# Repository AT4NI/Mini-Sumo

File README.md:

# Mini-Sumo
Codes and documentation for my minisumo robot.
It is focused on the development of competition robots made by me.
The repository will include: 3D models, code, PCB and electronic schematics.

**NOTE: The projects developed may have errors that will be corrected in the future.**

*The projects marked in italic are projects that are still on progress*

# Why did I make a repository?
It was made for fans of robotics competition, helping them to get access to information.
I would like any fan to be able to make their own robots and have fun.
Also, I would like to have version control of my projects.

# Folders

## Robots
- I7ACH1: Minisumo with 4 sensors and 2 line sensor
- GYU: Minisumo with 4 sensors and 2 line sensor
- SIRUKI: Microsumo with 3 sensors and 1 line sensor
- ALO: Microsumo with 2 sensors and 1 line sensor
- ATANI: Amateur RC Minisumo
## PCB's
- Main boards:
  - *SIRUKI: PCB designed for micro-sumo.*

## Code
- I7ach1: main code used for minisumo robot I7ach1 which uses a ESP32-C3 as the main board
- GYU: main code used for minisumo robot GYU which uses a ARDUINO NANO as the main controller
- *SIRUKI: main code used for microsumo robot SIRUKI which uses a ESP32-C3 as the main controller*
- ALO: main code used for microsumo robot ALO which uses a ESP32-C3 as the main controller
- ATANI: main code used for minisumo robot ATANI which uses a ARDUINO NANO as the main controller
## 3D Data
- Robots
	- I7ach1: Base of the robot is steel and the case is PLA.
	- *SIRUKI: Base of the robot is brass and the case is made of PLA*
	- *ALO: The robot is made of PLA*
	- ATANI: The robot is made of PLA.

# Software that I use
The software I use, most of them are free license and easy to use.
The formats of the files are the most friendly with the other types of software used.

- 3D data: I mainly use SOLIDWORKS and FUSION 360 but I upload the files in .IGES and .STL so you can use any 3D CAD software and slicer software out there to modify and/or print the parts.
- PCB's: I upload the gerbers in zip format for easy fabrication **[KiCad](https://www.kicad.org/)** which is a free and open source EDA.
- Code: I use ARDUINO IDE **[ARDUINO IDE ](https://www.arduino.cc/en/Guide)**  

---

*Developing robots, continue...*

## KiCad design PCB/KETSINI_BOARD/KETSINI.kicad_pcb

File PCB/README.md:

# PCB
### KETSINI_V1
PCB designed for micro-sumo.
 - **Brain:** ESP32 C3 Super Mini
 - **Driver:** DRV8871
 - **Voltage Regulator:** AMS1117-5

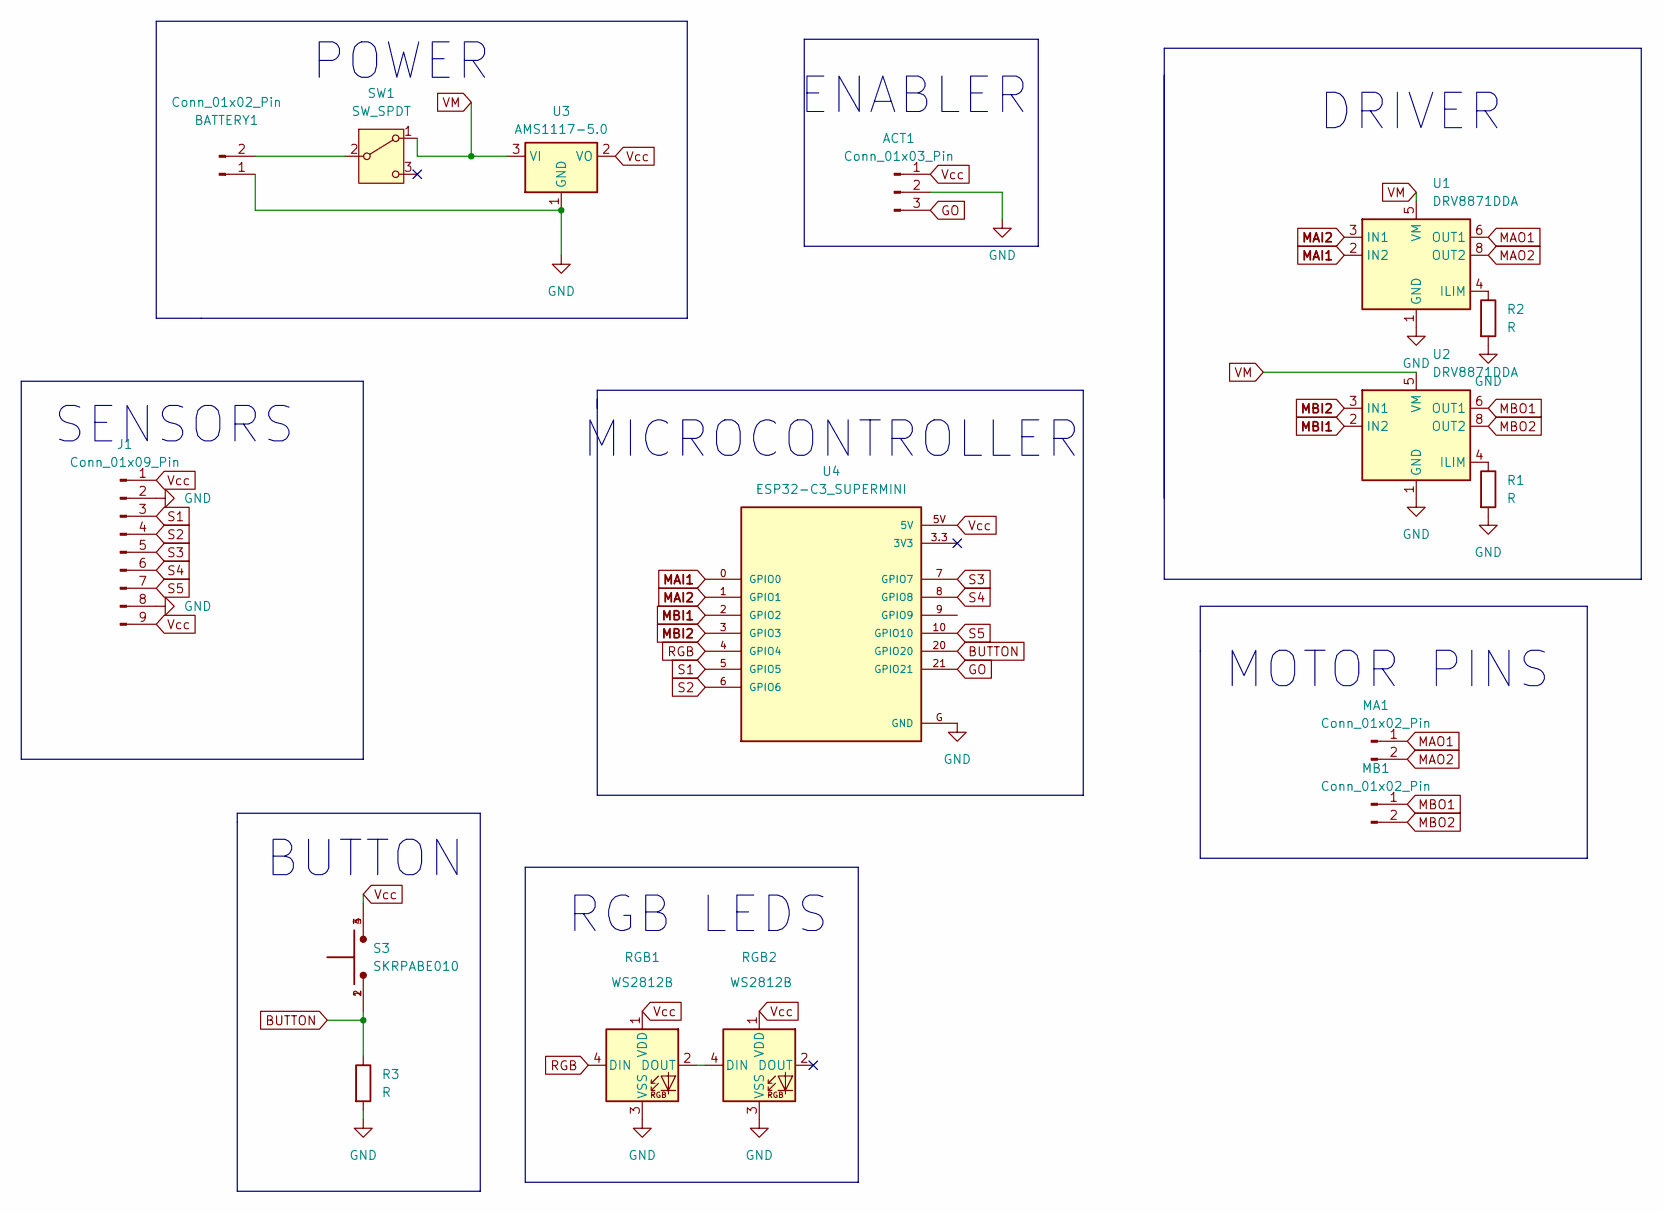
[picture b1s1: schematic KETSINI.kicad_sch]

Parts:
ACT1: Conn_01x03_Pin; PinHeader_1x03_P2.54mm_Vertical
BATTERY1: Conn_01x02_Pin; JST_EH_S2B-EH_1x02_P2.50mm_Horizontal
J1: Conn_01x09_Pin; PinSocket_1x09_P2.54mm_Vertical
MA1: Conn_01x02_Pin; PinHeader_1x02_P2.54mm_Vertical
MB1: Conn_01x02_Pin; PinHeader_1x02_P2.54mm_Vertical
R1, R2, R3: R; R_0805_2012Metric_Pad1.20x1.40mm_HandSolder
RGB1, RGB2: WS2812B; LED_WS2812B_PLCC4_5.0x5.0mm_P3.2mm
S3: SKRPABE010; SW_SKRPABE010
SW1: SW_SPDT; SW_SPDT_PCM12
U1, U2: DRV8871DDA; Texas_HTSOP-8-1EP_3.9x4.9mm_P1.27mm_EP2.95x4.9mm_Mask2.4x3.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
U3: AMS1117-5.0; SOT-223-3_TabPin2
U4: ESP32-C3_SUPERMINI; MODULE_ESP32-C3_SUPERMINI

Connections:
BUTTON: R3.1, S3.1, S3.2, U4.20 (GPIO20); also elsewhere on the board
GND: ACT1.2, BATTERY1.1, J1.2, J1.8, R1.2, R2.2, R3.2, RGB1.3 (VSS), RGB2.3 (VSS), U1.1 (GND), U1.7 (GND), U1.9 (GND), U2.1 (GND), U2.7 (GND), U2.9 (GND), U3.1 (GND), U4.G (GND); also elsewhere on the board
GO: ACT1.3, U4.21 (GPIO21); also elsewhere on the board
MAI1: U1.2 (IN2), U4.0 (GPIO0); also elsewhere on the board
MAI2: U1.3 (IN1), U4.1 (GPIO1); also elsewhere on the board
MAO1: MA1.1, U1.6 (OUT1)
MAO2: MA1.2, U1.8 (OUT2)
MBI1: U2.2 (IN2), U4.2 (GPIO2); also elsewhere on the board
MBI2: U2.3 (IN1), U4.3 (GPIO3); also elsewhere on the board
MBO1: MB1.1, U2.6 (OUT1)
MBO2: MB1.2, U2.8 (OUT2)
unnamed: BATTERY1.2, SW1.2 (B)
unnamed: RGB1.2 (DOUT), RGB2.4 (DIN)
unnamed: R2.1, U1.4 (ILIM)
unnamed: R1.1, U2.4 (ILIM)
RGB: RGB1.4 (DIN), U4.4 (GPIO4); also elsewhere on the board
S1: J1.3, U4.5 (GPIO5); also elsewhere on the board
S2: J1.4, U4.6 (GPIO6); also elsewhere on the board
S3: J1.5, U4.7 (GPIO7); also elsewhere on the board
S4: J1.6, U4.8 (GPIO8); also elsewhere on the board
S5: J1.7, U4.10 (GPIO10); also elsewhere on the board
VM: SW1.1 (A), U1.5 (VM), U2.5 (VM), U3.3 (VI)
Vcc: ACT1.1, J1.1, J1.9, RGB1.1 (VDD), RGB2.1 (VDD), S3.3, S3.4, U3.2 (VO), U4.5V; also elsewhere on the board

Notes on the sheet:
DRIVER
BUTTON
RGB LEDS
MOTOR PINS
SENSORS
POWER
MICROCONTROLLER
ENABLER

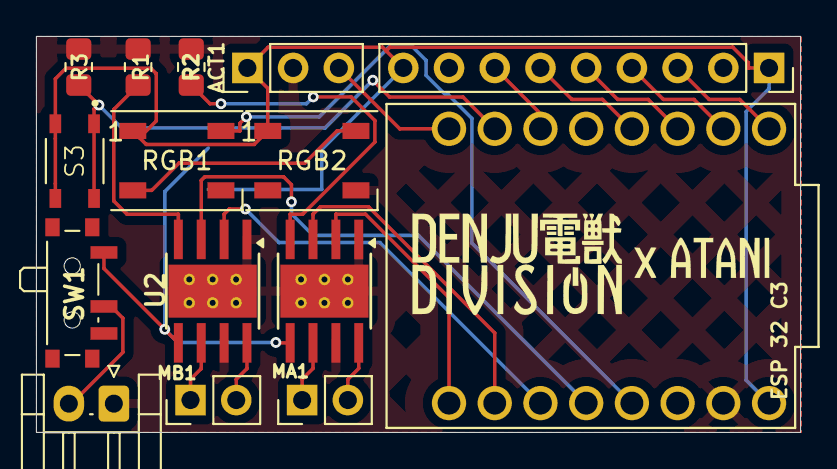
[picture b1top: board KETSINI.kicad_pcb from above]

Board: 2 copper layers, 42.4 x 22.0 mm, 16 parts (1 on the bottom side), 23 nets.

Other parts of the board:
ESP 32 C3: ESP32-C3_SUPERMINI; MODULE_ESP32-C3_SUPERMINI

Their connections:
BUTTON: ESP 32 C3.20 (GPIO20); also elsewhere on the board
GND: ESP 32 C3.G (GND); also elsewhere on the board
GO: ESP 32 C3.21 (GPIO21); also elsewhere on the board
MAI1: ESP 32 C3.0 (GPIO0); also elsewhere on the board
MAI2: ESP 32 C3.1 (GPIO1); also elsewhere on the board
MBI1: ESP 32 C3.2 (GPIO2); also elsewhere on the board
MBI2: ESP 32 C3.3 (GPIO3); also elsewhere on the board
RGB: ESP 32 C3.4 (GPIO4); also elsewhere on the board
S1: ESP 32 C3.5 (GPIO5); also elsewhere on the board
S2: ESP 32 C3.6 (GPIO6); also elsewhere on the board
S3: ESP 32 C3.7 (GPIO7); also elsewhere on the board
S4: ESP 32 C3.8 (GPIO8); also elsewhere on the board
S5: ESP 32 C3.10 (GPIO10); also elsewhere on the board
Vcc: ESP 32 C3.5V; also elsewhere on the board

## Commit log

2024-07-11 Create ESP32_C3_DRIVER_RC.ino
    I7ACHI Rc Mode
2024-07-11 CHANGE
2024-07-11 ADD_EXPLAIN
2024-07-11 KETZINI_UP_V1
2024-07-15 ATANI_MODEL
2024-07-15 CHANGE_MODE_ATANI
2024-07-15 CHANGE_MODEL
2024-08-29 Update ESP32_C3_DRIVER_RC.ino
    DRIFT
2024-12-12 3D_MODEL
    More 3D
2024-12-12 UPGRADE
2024-12-13 FUNCTION_BLE
2025-04-11 NEW_CODE
2025-05-26 UPGRADE_MAY
    3D_MODEL_CODE
2025-06-06 GYU_UPGRADE
2025-11-13 L4Z4USUP
    L4Z4US UP
